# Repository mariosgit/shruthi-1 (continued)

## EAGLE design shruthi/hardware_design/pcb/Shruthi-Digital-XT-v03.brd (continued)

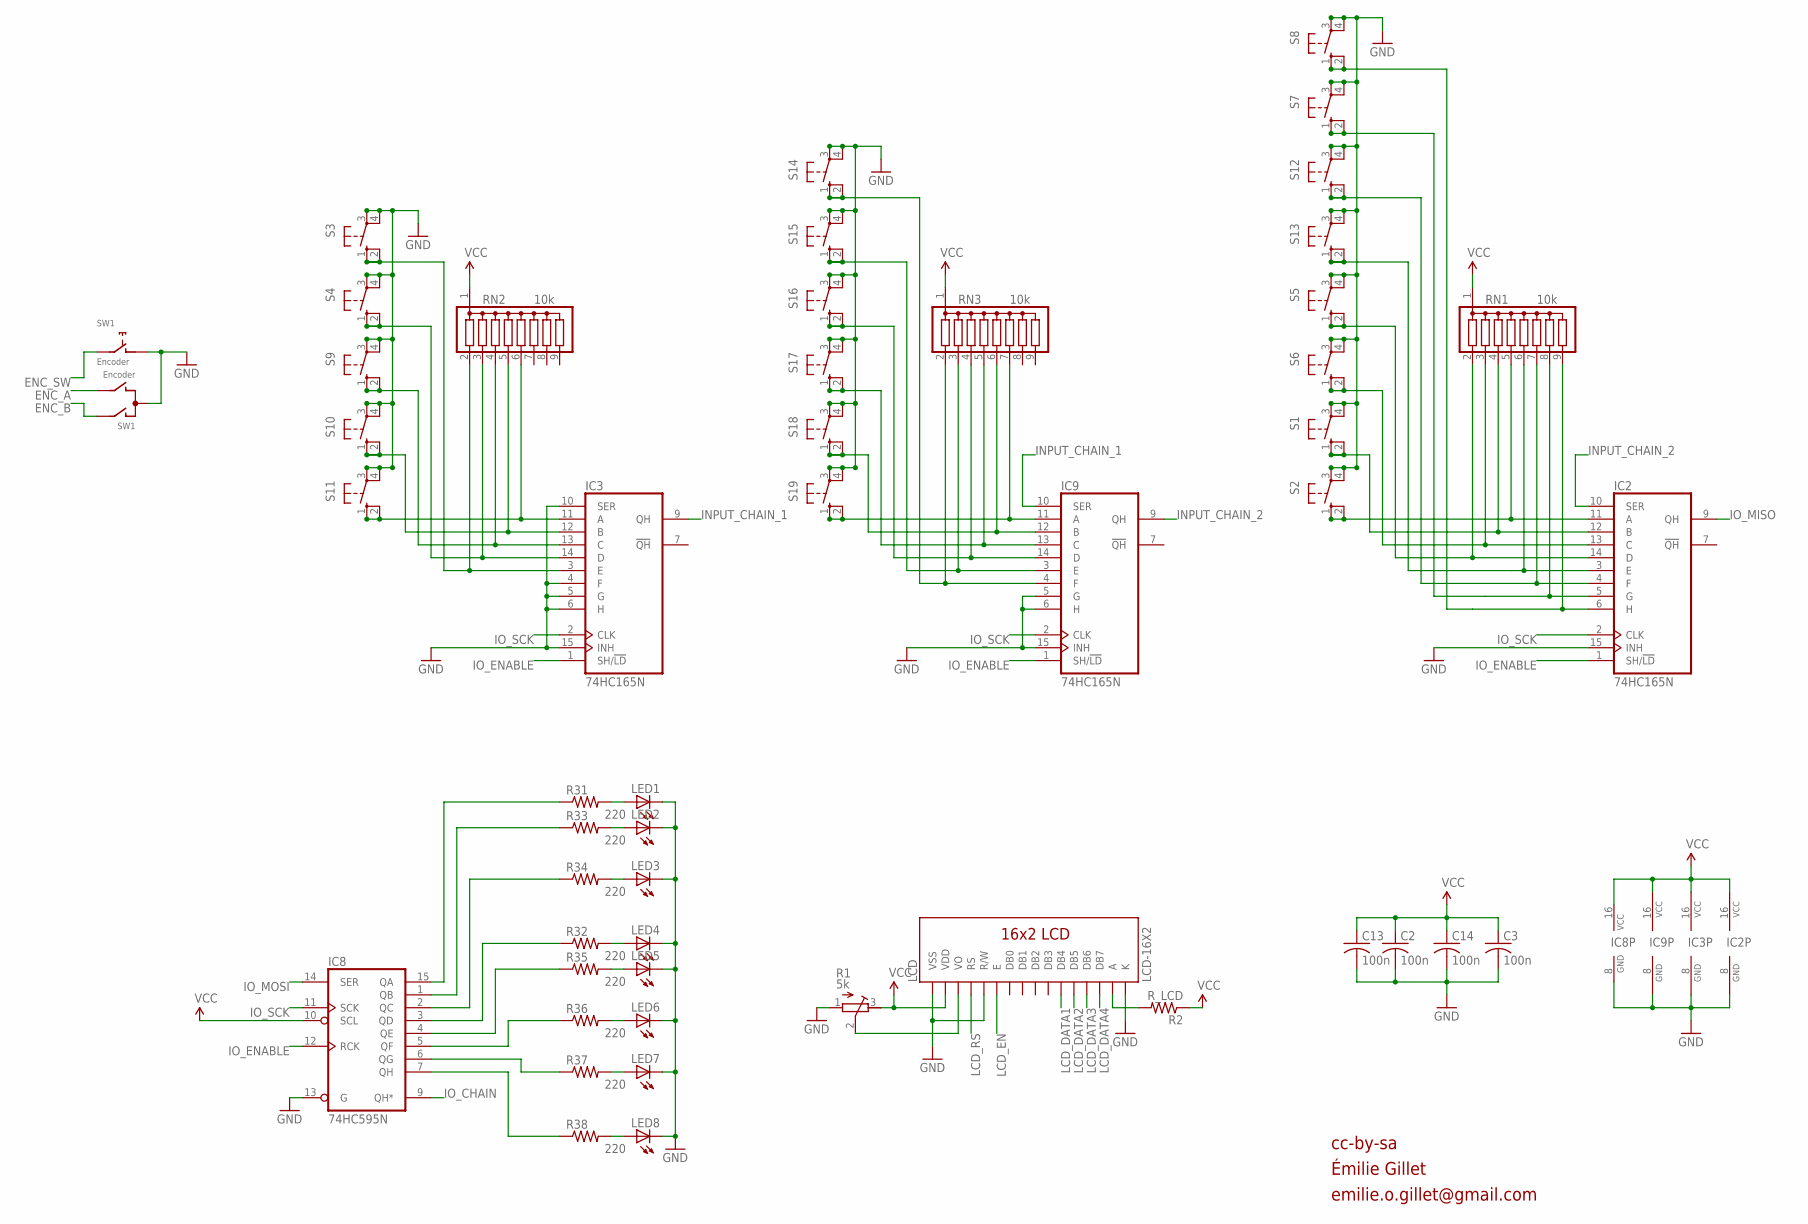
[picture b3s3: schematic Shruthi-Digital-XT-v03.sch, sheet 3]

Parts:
C2, C3, C13, C14: 100n; C025-024X044
IC2, IC3, IC9: 74HC165N; DIL16
IC8: 74HC595N; DIL16
LCD: LCD-16X2
LED1, LED2, LED3, LED4, LED5, LED6, LED7, LED8: LED3MM
R1: 5k; RTRIM3339P
R2: R_LCD; 0204/7
R31, R32, R33, R34, R35, R36, R37, R38: 220; 0204/7
RN1, RN2, RN3: 10k; SIL9
S1, S2, S3, S4, S5, S6, S7, S8, S9, S10, S11, S12, S13, S14, S15, S16, S17, S18, S19: 40-XX; B3F-40XX
SW1: Encoder; ALPS_EC12E_SW

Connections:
ENC_A: SW1.B; also elsewhere on the board
ENC_B: SW1.A; also elsewhere on the board
ENC_SW: SW1.E (2); also elsewhere on the board
GND: C2.2, C3.2, C13.2, C14.2, IC2.8 (GND), IC2.15 (INH), IC3.4 (F), IC3.5 (G), IC3.6 (H), IC3.8 (GND), IC3.10 (SER), IC3.15 (INH), IC8.8 (GND), IC8.13 (G), IC9.5 (G), IC9.6 (H), IC9.8 (GND), IC9.15 (INH), LCD.1 (VSS), LCD.5 (R/W), LCD.16 (K), LED1.K (C), LED2.K (C), LED3.K (C), LED4.K (C), LED5.K (C), LED6.K (C), LED7.K (C), LED8.K (C), R1.1 (E), S1.3, S1.4 (P1), S2.3, S2.4 (P1), S3.3, S3.4 (P1), S4.3, S4.4 (P1), S5.3, S5.4 (P1), S6.3, S6.4 (P1), S7.3, S7.4 (P1), S8.3, S8.4 (P1), S9.3, S9.4 (P1), S10.3, S10.4 (P1), S11.3, S11.4 (P1), S12.3, S12.4 (P1), S13.3, S13.4 (P1), S14.3, S14.4 (P1), S15.3, S15.4 (P1), S16.3, S16.4 (P1), S17.3, S17.4 (P1), S18.3, S18.4 (P1), S19.3, S19.4 (P1), SW1.C, SW1.D (1); also elsewhere on the board
INPUT_CHAIN_1: IC3.9 (QH), IC9.10 (SER)
INPUT_CHAIN_2: IC2.10 (SER), IC9.9 (QH)
IO_CHAIN: IC8.9 (QH*); also elsewhere on the board
IO_ENABLE: IC2.1 (SH/!LD), IC3.1 (SH/!LD), IC8.12 (RCK), IC9.1 (SH/!LD); also elsewhere on the board
IO_MISO: IC2.9 (QH); also elsewhere on the board
IO_MOSI: IC8.14 (SER); also elsewhere on the board
IO_SCK: IC2.2 (CLK), IC3.2 (CLK), IC8.11 (SCK), IC9.2 (CLK); also elsewhere on the board
LCD_DATA1: LCD.11 (DB4); also elsewhere on the board
LCD_DATA2: LCD.12 (DB5); also elsewhere on the board
LCD_DATA3: LCD.13 (DB6); also elsewhere on the board
LCD_DATA4: LCD.14 (DB7); also elsewhere on the board
LCD_EN: LCD.6 (E); also elsewhere on the board
LCD_RS: LCD.4 (RS); also elsewhere on the board
unnamed: IC8.2 (QC), R34.1
unnamed: IC9.11 (A), RN3.7, S19.1 (S), S19.2 (S1)
unnamed: IC9.3 (E), RN3.3, S15.1 (S), S15.2 (S1)
unnamed: IC2.4 (F), RN1.7, S12.1 (S), S12.2 (S1)
unnamed: IC2.14 (D), RN1.2, S5.1 (S), S5.2 (S1)
unnamed: IC2.13 (C), RN1.3, S6.1 (S), S6.2 (S1)
unnamed: IC2.12 (B), RN1.4, S1.1 (S), S1.2 (S1)
unnamed: IC2.11 (A), RN1.5, S2.1 (S), S2.2 (S1)
unnamed: IC2.3 (E), RN1.6, S13.1 (S), S13.2 (S1)
unnamed: IC2.5 (G), RN1.8, S7.1 (S), S7.2 (S1)
unnamed: IC2.6 (H), RN1.9, S8.1 (S), S8.2 (S1)
unnamed: IC8.15 (QA), R31.1
unnamed: IC8.1 (QB), R33.1
unnamed: IC8.3 (QD), R32.1
unnamed: IC8.4 (QE), R35.1
unnamed: IC8.5 (QF), R36.1
unnamed: IC8.7 (QH), R38.1
unnamed: IC8.6 (QG), R37.1
unnamed: IC3.14 (D), RN2.3, S4.1 (S), S4.2 (S1)
unnamed: IC3.13 (C), RN2.4, S9.1 (S), S9.2 (S1)
unnamed: IC3.12 (B), RN2.5, S10.1 (S), S10.2 (S1)
unnamed: IC3.11 (A), RN2.6, S11.1 (S), S11.2 (S1)
unnamed: LED1.A, R31.2
unnamed: LED2.A, R33.2
unnamed: LED3.A, R34.2
unnamed: LED4.A, R32.2
unnamed: LED5.A, R35.2
unnamed: LED6.A, R36.2
unnamed: LED7.A, R37.2
unnamed: LED8.A, R38.2
unnamed: IC3.3 (E), RN2.2, S3.1 (S), S3.2 (S1)
unnamed: IC9.4 (F), RN3.2, S14.1 (S), S14.2 (S1)
unnamed: IC9.14 (D), RN3.4, S16.1 (S), S16.2 (S1)
unnamed: IC9.13 (C), RN3.5, S17.1 (S), S17.2 (S1)
unnamed: IC9.12 (B), RN3.6, S18.1 (S), S18.2 (S1)
unnamed: LCD.3 (VO), R1.2 (S)
unnamed: LCD.15 (A), R2.2
VCC: C2.1, C3.1, C13.1, C14.1, IC2.16 (VCC), IC3.16 (VCC), IC8.10 (SCL), IC8.16 (VCC), IC9.16 (VCC), LCD.2 (VDD), R1.3 (A), R2.1, RN1.1, RN2.1, RN3.1; also elsewhere on the board

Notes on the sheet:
cc-by-sa
Émilie Gillet
emilie.o.gillet@gmail.com

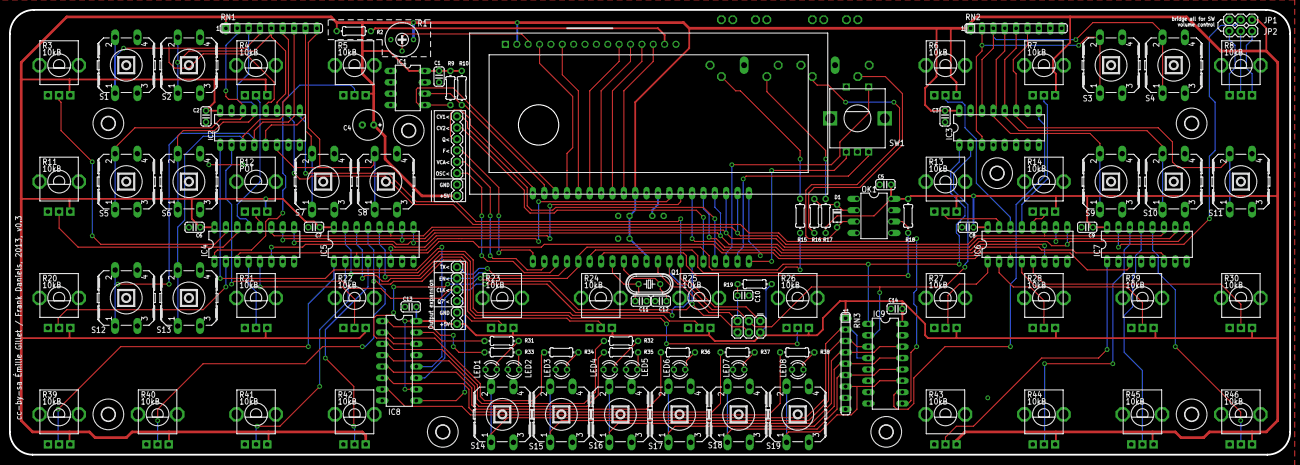
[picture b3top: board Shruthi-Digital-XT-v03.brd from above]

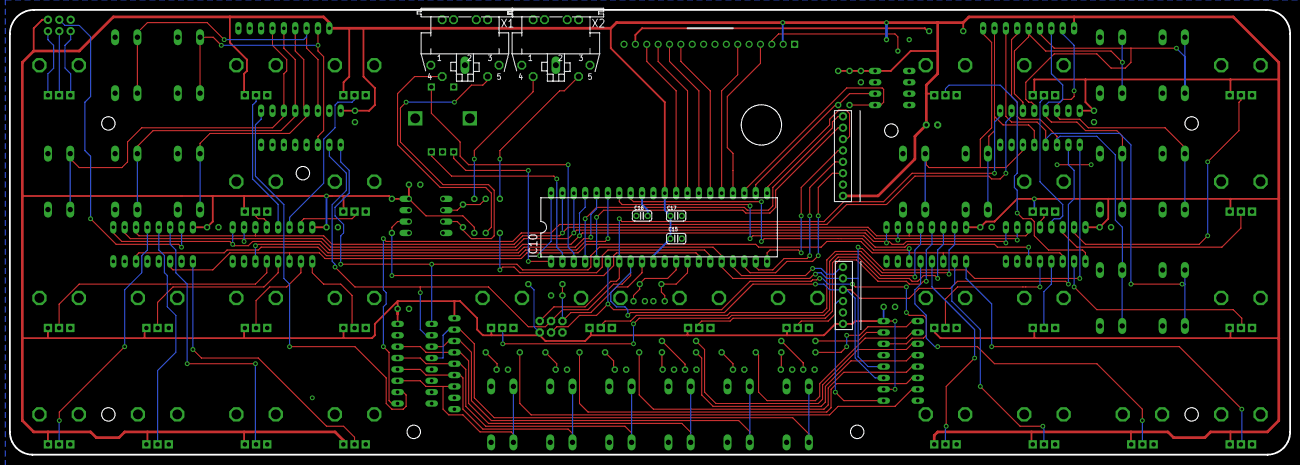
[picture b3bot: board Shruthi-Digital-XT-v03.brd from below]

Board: 2 copper layers, 286.0 x 99.4 mm, 128 parts (6 on the bottom side), 115 nets.

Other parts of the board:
U$1, U$3, U$4, U$6, U$7, U$8, U$10, U$11: 3,0
U$5: V2_LOGO_SHRUTHI_DIGITAL
U$9: V2_LOGO_DINGBAT1
